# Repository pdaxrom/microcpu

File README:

(c) 2020 sashz <sashz@pdaXrom.org>

For correct work with ftdi jtag, remove ftdi_sio module:

sudo rmmod  ftdi_sio

MICROCPU - 16-bit CPU

Registers:

The processor has eight 16-bit registers. The register 0 (PC) using as program counter.

0 - R0 - PC
1 - R1 - SP
2 - R2 - LR
3 - R3 - V0
4 - R4 - V1
5 - R5 - V2
6 - R6 - V3
7 - R7 - V4

Each register has high byte and low byte:

15 14 13 12 11 10 09 08 | 07 06 05 04 03 02 01 00
        HIGH BYTE       |        LOW BYTE

The processor has 7 addressing modes that can be used by the programmer:

1. Register
2. Immediate
3. Immediate indexed
4. Register indexed
5. Relative

The processor uses five condition code bits or flags:

I - interrupt mask
C - carry flag
Z - zero flag
V - 2s complement overflow
N - negative

Instructions

Machine instructions generally fall into three categories: data movement, arithmetic/logic, and control-flow.
We use the following notation:

<dst> Any destination register
<src> Any source register
<imm> 8-bit immediate
<imm16> 16-bit immediate
<idx> Any register or 4-bit unsigned immediate
<arg1> Any register
<arg2> Any register or 4-bit unsigned immediate
<rel> 11-bit signed immediate

Data Movement Instructions

LDRL <dst>, <src>, <idx> - Load low byte from source address + index
STRL <dst>, <src>, <idx> - Store low byte to source address + index
LDR  <dst>, <src>, <idx> - Load register (2 bytes) from source address + index
STR  <dst>, <src>, <idx> - Store register (2 bytes) to source address + index
SETL <dst>, <imm>        - Copy low byte from constant
SETH <dst>, <imm>        - Copy high byte from constant
MOVL <dst>, <src>        - Copy source low byte to destination low byte
MOVH <dst>, <src>        - Copy source low byte to destination high byte
MOV  <dst>, <src>        - Copy data from source to destination register

Little endian byte order using for LDR and STR.

Examples:
	SETL V0, 0
	SETH V0, $10
	LDRL V1, V0, 0
	SETL V2, 1
	SELH V2, 0
	STR  V1, V0, V2
	MOV V3, V2

Arithmetic and Logic Instructions

ADD  <dst>, <arg1>, <arg2> <dst> = <arg1> + <arg2>           Add
ADDC <dst>, <arg1>, <arg2> <dst> = <arg1> + <arg2>  + flag_C Add with carry
SUB  <dst>, <arg1>, <arg2> <dst> = <arg1> - <arg2>           Subtract
SUBC <dst>, <arg1>, <arg2> <dst> = <arg1> - <arg2>  - flag_C Subtract with carry
SHL  <dst>, <arg1>, <arg2> <dst> = <arg1> << <arg2>          Logic shift left
SHR  <dst>, <arg1>, <arg2> <dst> = <arg1> >> <arg2>          Logic shift right
AND  <dst>, <arg1>, <arg2> <dst> = <arg1> & <arg2>           And
OR   <dst>, <arg1>, <arg2> <dst> = <arg1> | <arg2>           Or
INV  <dst>, <arg1>         <dst> = ~<arg1>                   Inversion
XOR  <dst>, <arg1>, <arg2> <dst> = <arg1> ^ <arg2>           Exclusive Or
SXT  <dst>, <arg1>         <dst> = sign <arg1>               Sign extend

Examples:

	ADD V0, V1, V2
	ADDC V1, V2, 5
	SUB V0, V2, V1
	SHR V0, V0, 1
	SXT V1, V1

Control Flow Instructions

CMP <arg1>, <arg2> Compare
TST <arg1>, <arg2> Test bits

B   <rel> - Branch
BLE <rel> - Branch On Less Than Or Equal Zero
BGE <rel> - Branch On Greater Than Or Equal Zero
BEQ <rel> - Branch On Equal Zero
BCS <rel> - Branch If Carry Set

Examples:

	CMP V0, 0
	BEQ exit
	CMP V0, V1
	BLE loop
	TST V0, 4
	BEQ wait

Assembler directives

<symbol> EQU <exp>      Set a symbol equal to an expression
DB <imm>[,<imm>...]     Define constant byte(s)
DW <imm16>[,<imm16>...] Define constant word(s)
DS <imm16>[,<imm>]      Reserves num bytes of space and initializes them to val (optional, defaul 0).
ALIGN <imm>             Align address to num bytes

Examples:
CONST_ONE EQU 1
CONST_TWO EQU 2
	DB 1, $2, $3, 4, 5
	DB "Hello, World", 0
	DB 'About'
	DW $1234, 8192, 0
	DS 32
	DS 64,$FF
	ALIGN 4

Accembler macro definition

MACRO <name> Start macro
ENDM         End macro

macro parameters start with # and are numbered from 1.

Example:

	MACRO SET
	SETH	#1, /#2
	SETL	#1, #2
	ENDM

	SET V0, $1234

Assembler procedures

<label> PROC                Start procedure
GLOBAL <label>[,<label>...] Add local procedure label as global
ENDP                        End procedure

Example:

get_one PROC
	SET V0, 1
	ADD PC, LR, 3
	ENDP
	
get_1	PROC
	GLOBAL get_2
	SET V0, 1
return	ADD PC, LR, 3
get_2	SET V0, 2
	B return
	ENDP

Microassembler optios:

microasm [-verilog|-binary] <input.asm> [output]

-verilog - create verilog ram file

-binary  - create binary file

By default, the output file is hex file.

Bootloader options:

bootloader <uart port> load <file.bin> [<start address> [<end address>]]

bootloader <uart port> load <file.bin> <start address> <end address>

bootloader <uart port> go [<address>]

load - load a binary file to RAM

save - save RAM to a binary file

go - execute code

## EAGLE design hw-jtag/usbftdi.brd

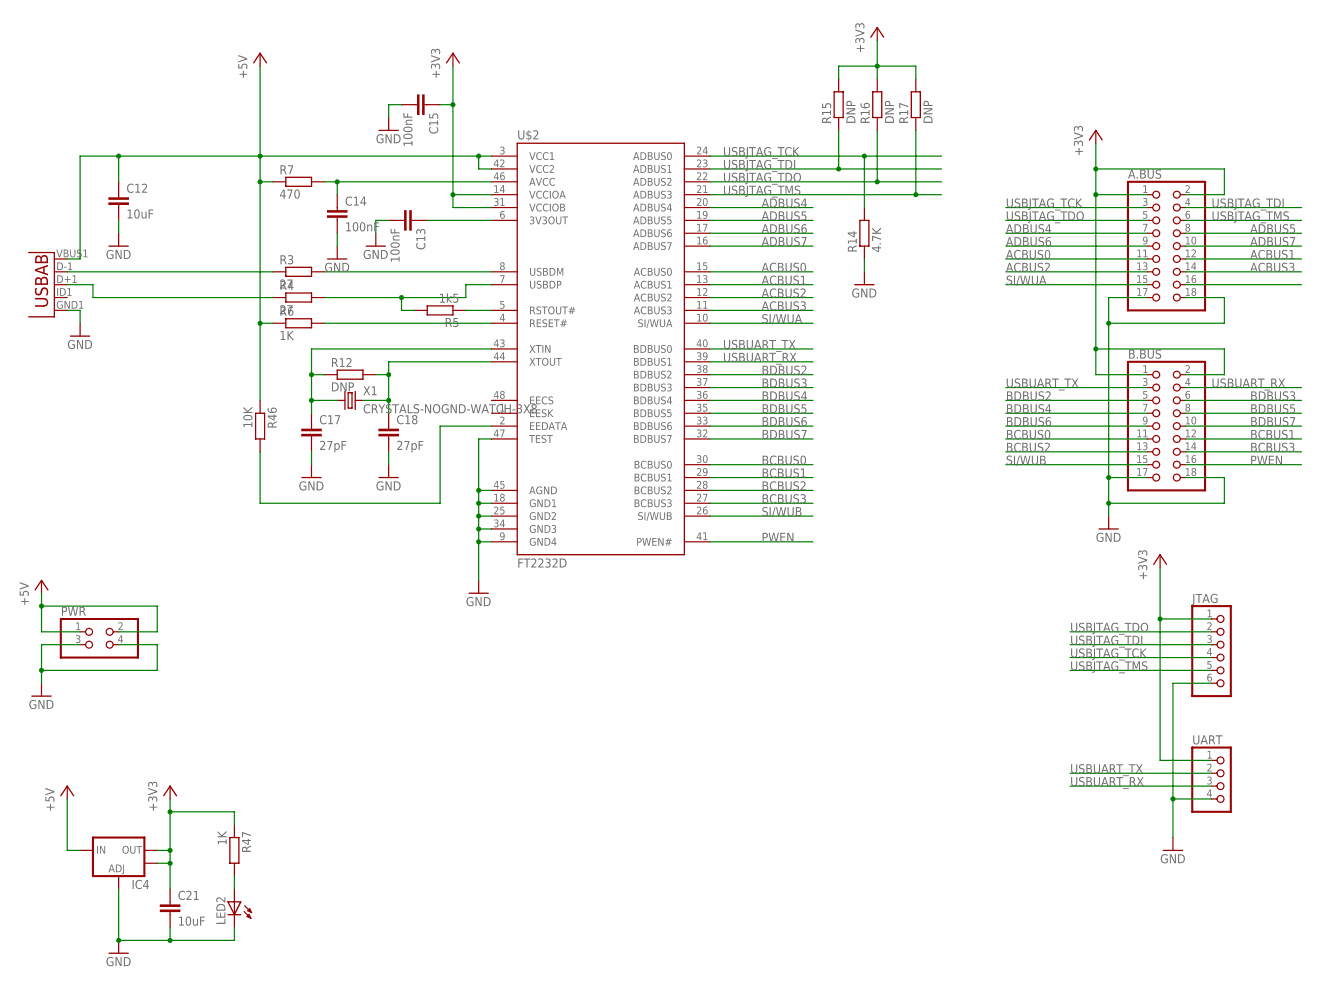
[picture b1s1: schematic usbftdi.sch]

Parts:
A.BUS: PINHD-2X9; 2X09
B.BUS: PINHD-2X9; 2X09
C12, C21: 10uF; C0805
C13, C14, C15: 100nF; C0603
C17, C18: 27pF; C0603
IC4: V_REG_LM1117SOT223; SOT223
JTAG: PINHD-1X6; 1X06
LED2: LEDCHIPLED_0603; CHIPLED_0603
MICROUSB: USB""; USB-MICRO-SMD
PWR: PINHD-2X2; 2X02
R3, R4: 27; R0603
R5: 1k5; R0603
R6, R47: 1K; R0603
R7: 470; R0603
R12, R15, R16, R17: DNP; R0603
R14: 4.7K; R0603
R46: 10K; R0603
U$2: FT2232D; LQFP-48
UART: PINHD-1X4; 1X04
X1: CRYSTALS-NOGND-WATCH-3X8; WATCH-3X8

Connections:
+3V3: A.BUS.1, A.BUS.2, B.BUS.1, B.BUS.2, C15.1, C21.1, IC4.2 (OUT), IC4.4 (OUT), JTAG.1, R15.2, R16.2, R17.2, R47.1, U$2.14 (VCCIOA), U$2.31 (VCCIOB), UART.1
+5V: C12.1, IC4.3 (IN), MICROUSB.VBUS1 (VBUS), PWR.1, PWR.2, R6.1, R7.1, R46.1, U$2.3 (VCC1), U$2.42 (VCC2)
ACBUS0: A.BUS.11, U$2.15 (ACBUS0)
ACBUS1: A.BUS.12, U$2.13 (ACBUS1)
ACBUS2: A.BUS.13, U$2.12 (ACBUS2)
ACBUS3: A.BUS.14, U$2.11 (ACBUS3)
ADBUS4: A.BUS.7, U$2.20 (ADBUS4)
ADBUS5: A.BUS.8, U$2.19 (ADBUS5)
ADBUS6: A.BUS.9, U$2.17 (ADBUS6)
ADBUS7: A.BUS.10, U$2.16 (ADBUS7)
BCBUS0: B.BUS.11, U$2.30 (BCBUS0)
BCBUS1: B.BUS.12, U$2.29 (BCBUS1)
BCBUS2: B.BUS.13, U$2.28 (BCBUS2)
BCBUS3: B.BUS.14, U$2.27 (BCBUS3)
BDBUS2: B.BUS.5, U$2.38 (BDBUS2)
BDBUS3: B.BUS.6, U$2.37 (BDBUS3)
BDBUS4: B.BUS.7, U$2.36 (BDBUS4)
BDBUS5: B.BUS.8, U$2.35 (BDBUS5)
BDBUS6: B.BUS.9, U$2.33 (BDBUS6)
BDBUS7: B.BUS.10, U$2.32 (BDBUS7)
GND: A.BUS.17, A.BUS.18, B.BUS.17, B.BUS.18, C12.2, C13.2, C14.2, C15.2, C17.2, C18.2, C21.2, IC4.1 (ADJ), JTAG.6, LED2.C, MICROUSB.GND1 (GND), PWR.3, PWR.4, R14.1, U$2.9 (GND4), U$2.18 (GND1), U$2.25 (GND2), U$2.34 (GND3), U$2.45 (AGND), U$2.47 (TEST), UART.4
unnamed: MICROUSB.D-1 (D-), R3.1
unnamed: MICROUSB.D+1 (D+), R4.1
unnamed: R3.2, U$2.8 (USBDM)
unnamed: C13.1, U$2.6 (3V3OUT)
unnamed: C14.1, R7.2, U$2.46 (AVCC)
unnamed: R4.2, R5.2, U$2.7 (USBDP)
unnamed: R5.1, U$2.5 (RSTOUT#)
unnamed: R6.2, U$2.4 (RESET#)
unnamed: C17.1, R12.1, U$2.43 (XTIN), X1.1
unnamed: C18.1, R12.2, U$2.44 (XTOUT), X1.2
unnamed: R46.2, U$2.2 (EEDATA)
unnamed: LED2.A, R47.2
PWEN: B.BUS.16, U$2.41 (PWEN#)
SI/WUA: A.BUS.15, U$2.10 (SI/WUA)
SI/WUB: B.BUS.15, U$2.26 (SI/WUB)
USBJTAG_TCK: A.BUS.3, JTAG.4, R14.2, U$2.24 (ADBUS0)
USBJTAG_TDI: A.BUS.4, JTAG.3, R15.1, U$2.23 (ADBUS1)
USBJTAG_TDO: A.BUS.5, JTAG.2, R16.1, U$2.22 (ADBUS2)
USBJTAG_TMS: A.BUS.6, JTAG.5, R17.1, U$2.21 (ADBUS3)
USBUART_RX: B.BUS.4, U$2.39 (BDBUS1), UART.3
USBUART_TX: B.BUS.3, U$2.40 (BDBUS0), UART.2

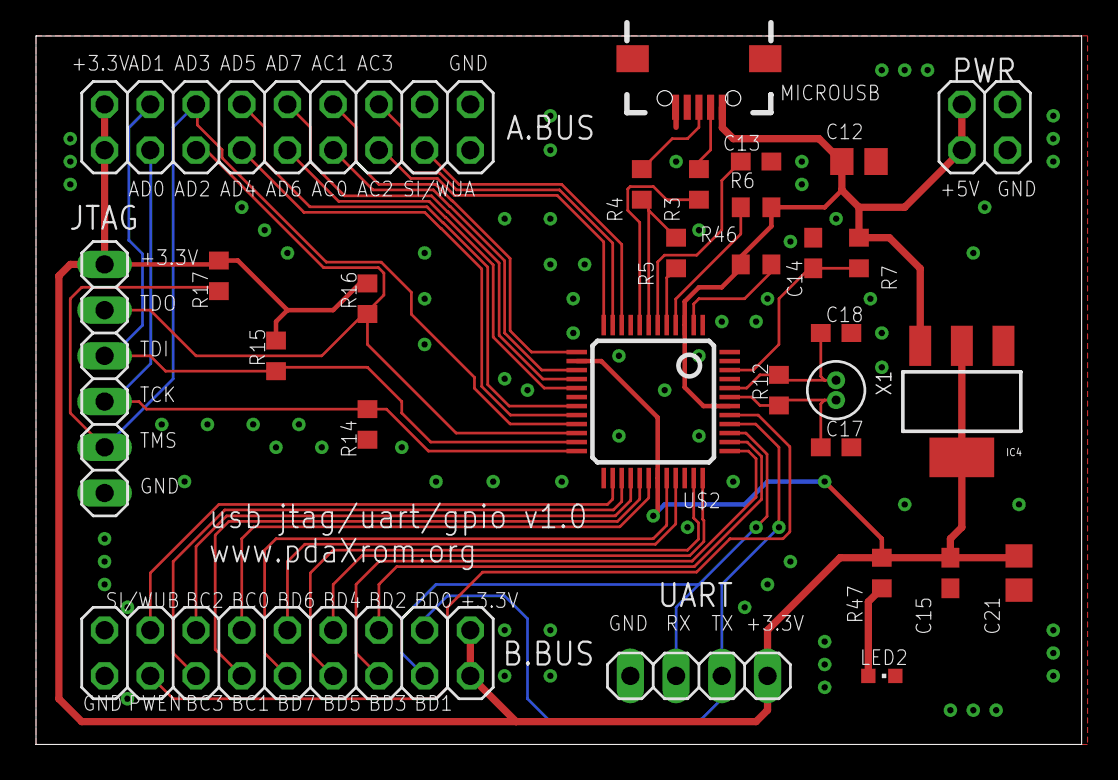
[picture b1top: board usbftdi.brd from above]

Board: 2 copper layers, 58.1 x 39.4 mm, 29 parts (0 on the bottom side), 42 nets.

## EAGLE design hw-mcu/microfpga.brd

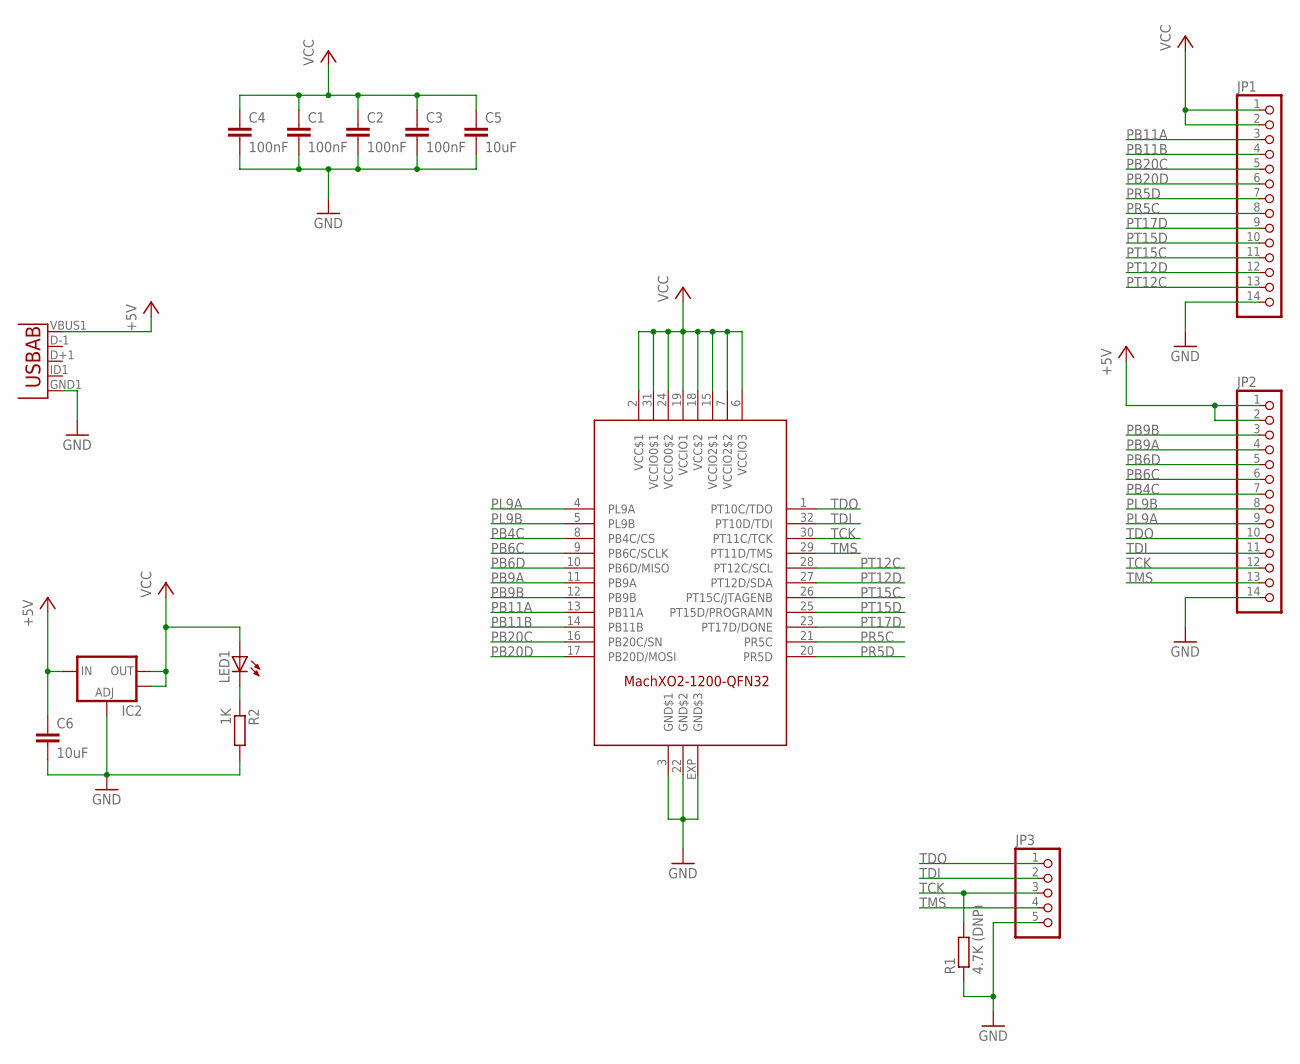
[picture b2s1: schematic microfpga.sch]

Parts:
C1, C2, C3, C4: 100nF; C0603
C5, C6: 10uF; C0805
IC2: V_REG_LM1117SOT223; SOT223
JP1, JP2: PINHD-1X14; 1X14
JP3: PINHD-1X5; 1X05
LED1: LEDCHIPLED_0603; CHIPLED_0603
R1: 4.7K (DNP); R0603
R2: 1K; R0603
U2: USB""; USB-MICRO-SMD
U$1: MACHXO2-1200; QFN32

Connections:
+5V: C6.1, IC2.3 (IN), JP2.1, JP2.2, U2.VBUS1 (VBUS)
GND: C1.2, C2.2, C3.2, C4.2, C5.2, C6.2, IC2.1 (ADJ), JP1.14, JP2.14, JP3.5, R1.1, R2.2, U2.GND1 (GND), U$1.3 (GND$1), U$1.22 (GND$2), U$1.EXP (GND$3)
unnamed: LED1.C, R2.1
PB4C: JP2.7, U$1.8 (PB4C/CS)
PB6C: JP2.6, U$1.9 (PB6C/SCLK)
PB6D: JP2.5, U$1.10 (PB6D/MISO)
PB9A: JP2.4, U$1.11 (PB9A)
PB9B: JP2.3, U$1.12 (PB9B)
PB11A: JP1.3, U$1.13 (PB11A)
PB11B: JP1.4, U$1.14 (PB11B)
PB20C: JP1.5, U$1.16 (PB20C/SN)
PB20D: JP1.6, U$1.17 (PB20D/MOSI)
PL9A: JP2.9, U$1.4 (PL9A)
PL9B: JP2.8, U$1.5 (PL9B)
PR5C: JP1.8, U$1.21 (PR5C)
PR5D: JP1.7, U$1.20 (PR5D)
PT12C: JP1.13, U$1.28 (PT12C/SCL)
PT12D: JP1.12, U$1.27 (PT12D/SDA)
PT15C: JP1.11, U$1.26 (PT15C/JTAGENB)
PT15D: JP1.10, U$1.25 (PT15D/PROGRAMN)
PT17D: JP1.9, U$1.23 (PT17D/DONE)
TCK: JP2.12, JP3.3, R1.2, U$1.30 (PT11C/TCK)
TDI: JP2.11, JP3.2, U$1.32 (PT10D/TDI)
TDO: JP2.10, JP3.1, U$1.1 (PT10C/TDO)
TMS: JP2.13, JP3.4, U$1.29 (PT11D/TMS)
VCC: C1.1, C2.1, C3.1, C4.1, C5.1, IC2.2 (OUT), IC2.4 (OUT), JP1.1, JP1.2, LED1.A, U$1.2 (VCC$1), U$1.6 (VCCIO3), U$1.7 (VCCIO2$2), U$1.15 (VCCIO2$1), U$1.18 (VCC$2), U$1.19 (VCCIO1), U$1.24 (VCCIO0$2), U$1.31 (VCCIO0$1)

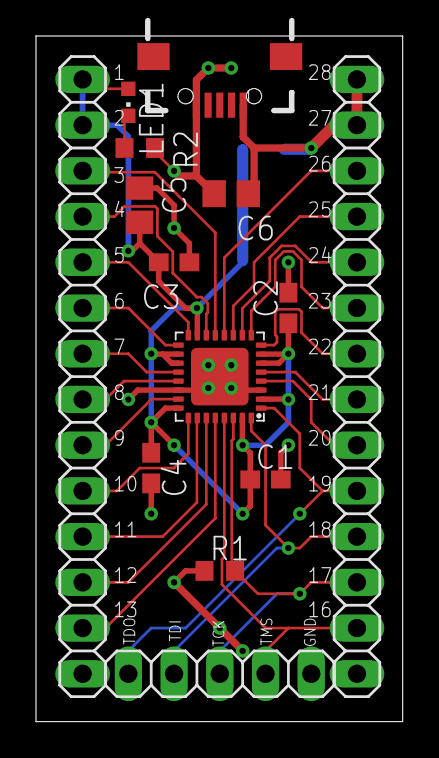
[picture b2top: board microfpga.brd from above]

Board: 2 copper layers, 20.4 x 38.1 mm, 15 parts (1 on the bottom side), 26 nets.

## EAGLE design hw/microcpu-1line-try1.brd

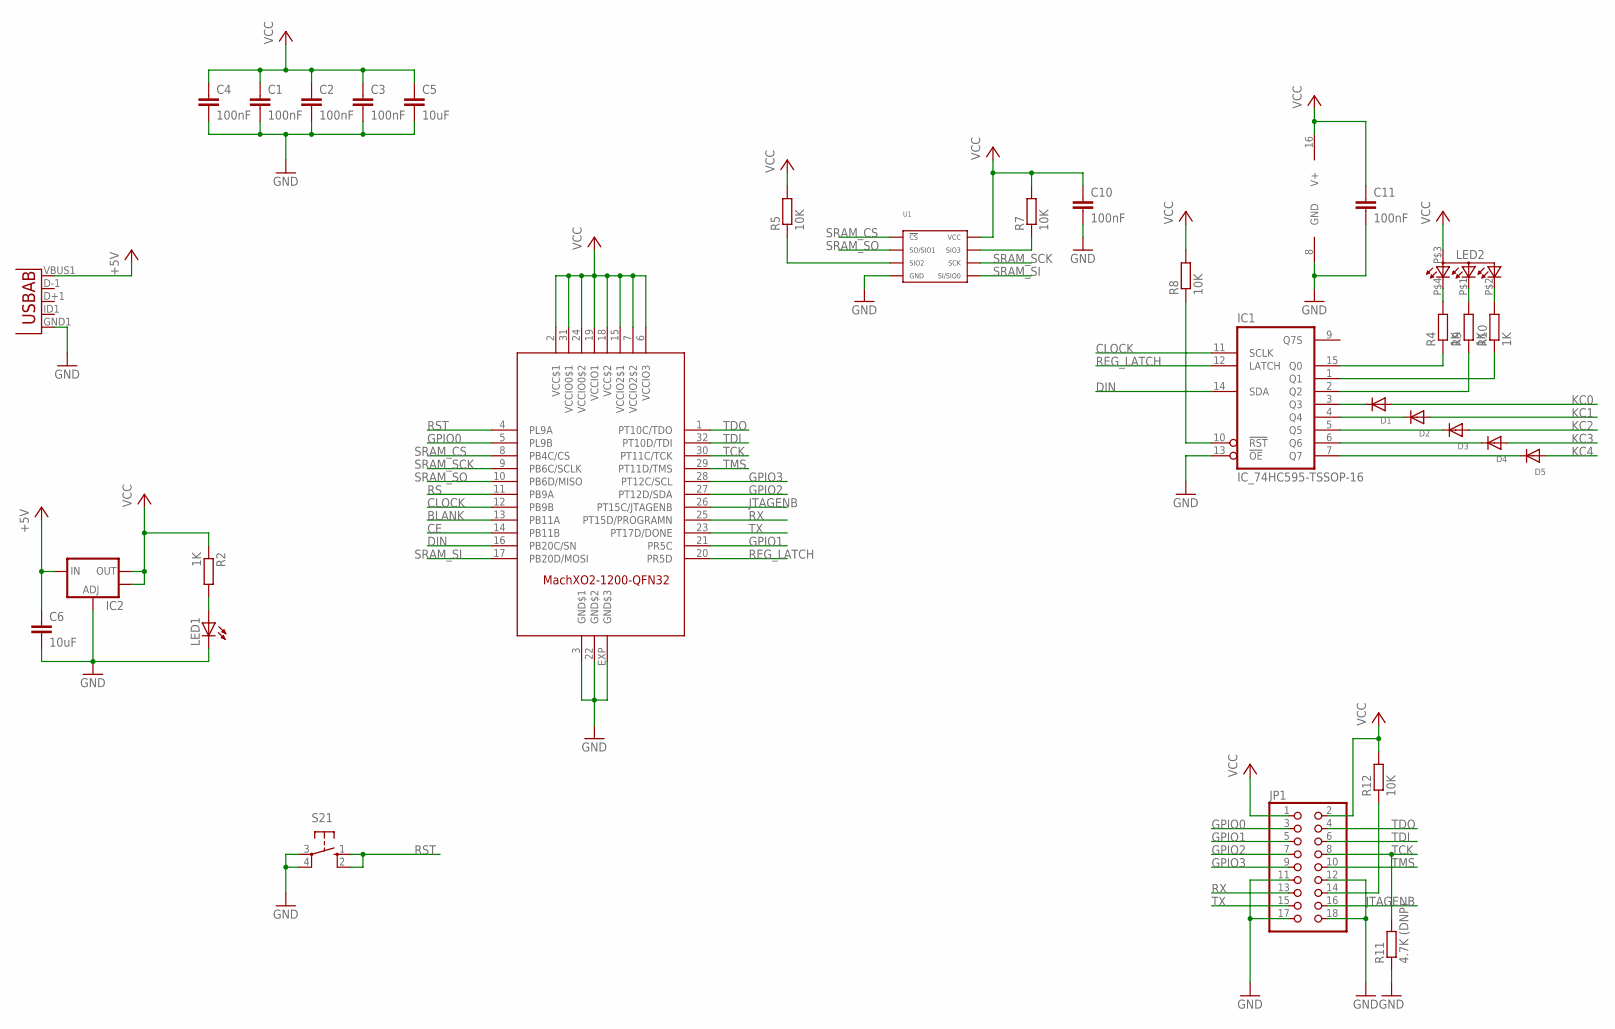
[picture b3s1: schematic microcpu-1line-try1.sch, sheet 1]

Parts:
C1, C2, C3, C4, C10, C11: 100nF; C0603
C5, C6: 10uF; C0805
D1, D2, D3, D4, D5: DIODESOD-123; SOD-123
IC1: IC_74HC595-TSSOP-16; TSSOP-16
IC2: V_REG_LM1117SOT223; SOT223
JP1: PINHD-2X9/90; 2X09/90
LED1: LEDCHIPLED_0603; CHIPLED_0603
LED2: 19-237/R6GHBHC-A04/2T
R2, R4, R9, R10: 1K; R0603
R5, R7, R8, R12: 10K; R0603
R11: 4.7K (DNP); R0603
S21: 10-XX; B3F-10XX
U1: 23A1024/23LC1024-I/SN; 23A1024_SOIC-8
U2: USB""; USB-MICRO-SMD
U$1: MACHXO2-1200; QFN32

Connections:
+5V: C6.1, IC2.3 (IN), U2.VBUS1 (VBUS)
BLANK: U$1.13 (PB11A); also elsewhere on the board
CE: U$1.14 (PB11B); also elsewhere on the board
CLOCK: IC1.11 (SCLK), U$1.12 (PB9B); also elsewhere on the board
DIN: IC1.14 (SDA), U$1.16 (PB20C/SN); also elsewhere on the board
GND: C1.2, C2.2, C3.2, C4.2, C5.2, C6.2, C10.2, C11.2, IC1.8 (GND), IC1.13 (!OE), IC2.1 (ADJ), JP1.11, JP1.12, JP1.17, JP1.18, LED1.C, R11.1, S21.3, S21.4 (P1), U1.4 (GND), U2.GND1 (GND), U$1.3 (GND$1), U$1.22 (GND$2), U$1.EXP (GND$3); also elsewhere on the board
GPIO0: JP1.3, U$1.5 (PL9B)
GPIO1: JP1.5, U$1.21 (PR5C)
GPIO2: JP1.7, U$1.27 (PT12D/SDA)
GPIO3: JP1.9, U$1.28 (PT12C/SCL)
JTAGENB: JP1.16, U$1.26 (PT15C/JTAGENB)
KC0: D1.A; also elsewhere on the board
KC1: D2.A; also elsewhere on the board
KC2: D3.A; also elsewhere on the board
KC3: D4.A; also elsewhere on the board
KC4: D5.A; also elsewhere on the board
unnamed: LED1.A, R2.2
unnamed: R7.1, U1.7 (SIO3)
unnamed: IC1.10 (!RST), R8.1
unnamed: R5.1, U1.3 (SIO2)
unnamed: LED2.P$4 (CRED), R4.2
unnamed: LED2.P$1 (CBLUE), R9.2
unnamed: LED2.P$2 (CGREEN), R10.2
unnamed: IC1.15 (Q0), R4.1
unnamed: IC1.1 (Q1), R10.1
unnamed: IC1.2 (Q2), R9.1
unnamed: JP1.14, R12.1
unnamed: D1.C, IC1.3 (Q3)
unnamed: D2.C, IC1.4 (Q4)
unnamed: D3.C, IC1.5 (Q5)
unnamed: D4.C, IC1.6 (Q6)
unnamed: D5.C, IC1.7 (Q7)
REG_LATCH: IC1.12 (LATCH), U$1.20 (PR5D)
RS: U$1.11 (PB9A); also elsewhere on the board
RST: S21.1 (S), S21.2 (S1), U$1.4 (PL9A)
RX: JP1.13, U$1.25 (PT15D/PROGRAMN)
SRAM_CS: U1.1 (CS'), U$1.8 (PB4C/CS)
SRAM_SCK: U1.6 (SCK), U$1.9 (PB6C/SCLK)
SRAM_SI: U1.5 (SI/SIO0), U$1.17 (PB20D/MOSI)
SRAM_SO: U1.2 (SO/SIO1), U$1.10 (PB6D/MISO)
TCK: JP1.8, R11.2, U$1.30 (PT11C/TCK); also elsewhere on the board
TDI: JP1.6, U$1.32 (PT10D/TDI); also elsewhere on the board
TDO: JP1.4, U$1.1 (PT10C/TDO); also elsewhere on the board
TMS: JP1.10, U$1.29 (PT11D/TMS); also elsewhere on the board
TX: JP1.15, U$1.23 (PT17D/DONE)
VCC: C1.1, C2.1, C3.1, C4.1, C5.1, C10.1, C11.1, IC1.16 (V+), IC2.2 (OUT), IC2.4 (OUT), JP1.1, JP1.2, LED2.P$3 (A), R2.1, R5.2, R7.2, R8.2, R12.2, U1.8 (VCC), U$1.2 (VCC$1), U$1.6 (VCCIO3), U$1.7 (VCCIO2$2), U$1.15 (VCCIO2$1), U$1.18 (VCC$2), U$1.19 (VCCIO1), U$1.24 (VCCIO0$2), U$1.31 (VCCIO0$1); also elsewhere on the board

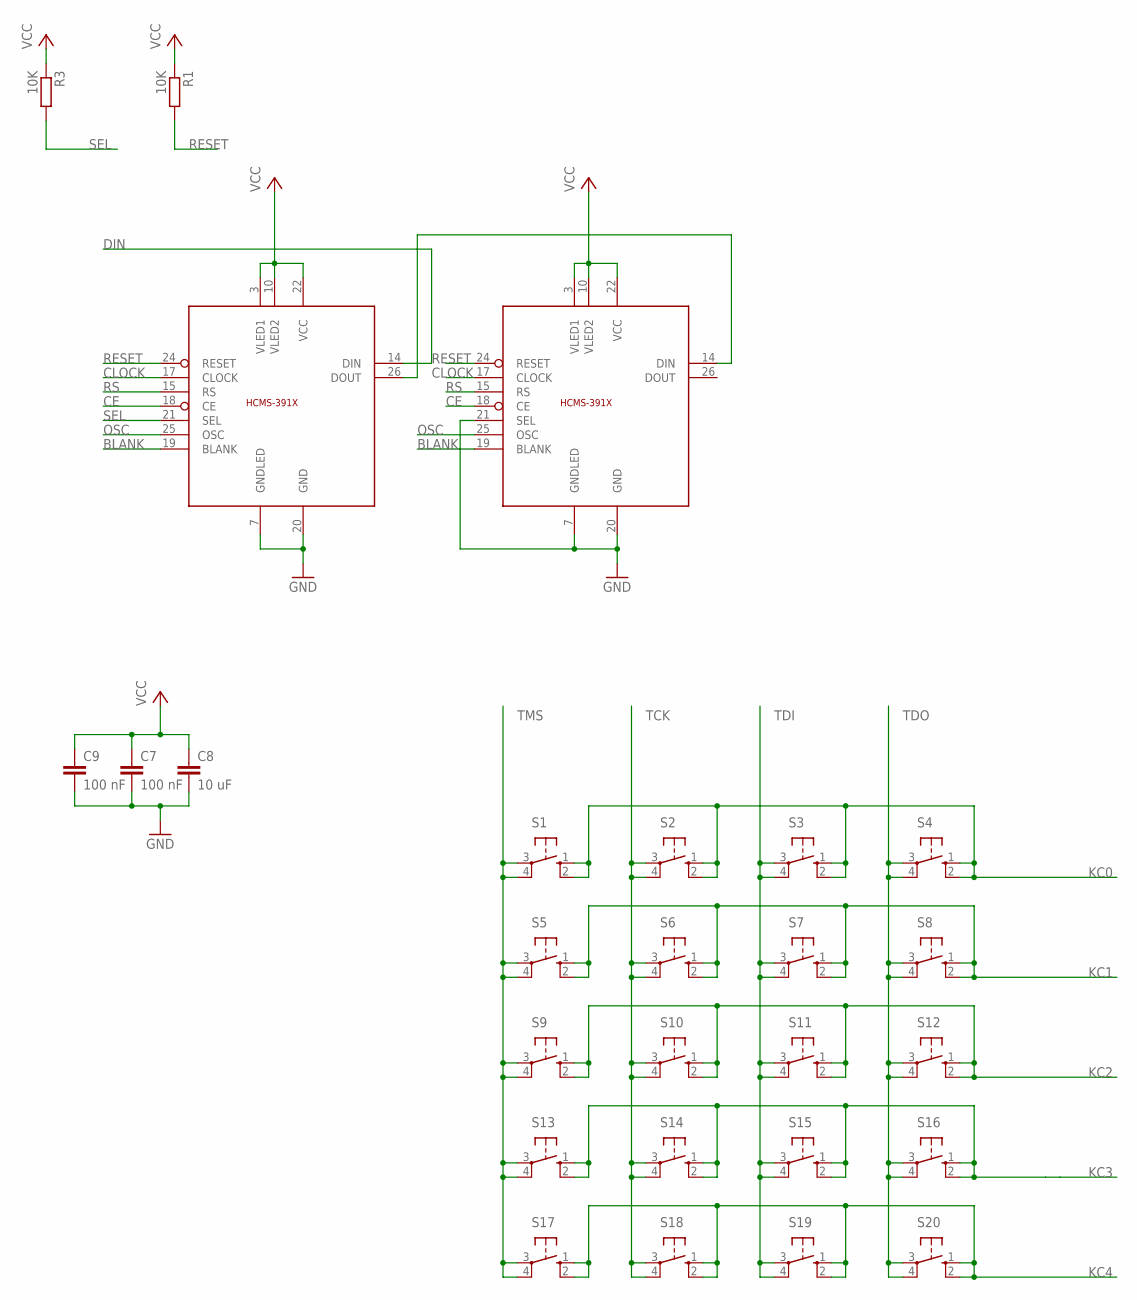
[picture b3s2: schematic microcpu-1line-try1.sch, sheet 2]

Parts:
C7, C9: 100 nF; C0603K
C8: 10 uF; C0805K
R1, R3: 10K; R0603
S1, S2, S3, S4, S5, S6, S7, S8, S9, S10, S11, S12, S13, S14, S15, S16, S17, S18, S19, S20: 10-XX; B3F-10XX
U$2, U$3: HCMS-391X

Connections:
BLANK: U$2.19 (BLANK), U$3.19 (BLANK); also elsewhere on the board
CE: U$2.18 (CE), U$3.18 (CE); also elsewhere on the board
CLOCK: U$2.17 (CLOCK), U$3.17 (CLOCK); also elsewhere on the board
DIN: U$2.14 (DIN); also elsewhere on the board
GND: C7.2, C8.2, C9.2, U$2.7 (GNDLED), U$2.20 (GND), U$3.7 (GNDLED), U$3.20 (GND), U$3.21 (SEL); also elsewhere on the board
KC0: S1.1 (S), S1.2 (S1), S2.1 (S), S2.2 (S1), S3.1 (S), S3.2 (S1), S4.1 (S), S4.2 (S1); also elsewhere on the board
KC1: S5.1 (S), S5.2 (S1), S6.1 (S), S6.2 (S1), S7.1 (S), S7.2 (S1), S8.1 (S), S8.2 (S1); also elsewhere on the board
KC2: S9.1 (S), S9.2 (S1), S10.1 (S), S10.2 (S1), S11.1 (S), S11.2 (S1), S12.1 (S), S12.2 (S1); also elsewhere on the board
KC3: S13.1 (S), S13.2 (S1), S14.1 (S), S14.2 (S1), S15.1 (S), S15.2 (S1), S16.1 (S), S16.2 (S1); also elsewhere on the board
KC4: S17.1 (S), S17.2 (S1), S18.1 (S), S18.2 (S1), S19.1 (S), S19.2 (S1), S20.1 (S), S20.2 (S1); also elsewhere on the board
unnamed: U$2.26 (DOUT), U$3.14 (DIN)
OSC: U$2.25 (OSC), U$3.25 (OSC)
RESET: R1.2, U$2.24 (RESET), U$3.24 (RESET)
RS: U$2.15 (RS), U$3.15 (RS); also elsewhere on the board
SEL: R3.2, U$2.21 (SEL)
TCK: S2.3, S2.4 (P1), S6.3, S6.4 (P1), S10.3, S10.4 (P1), S14.3, S14.4 (P1), S18.3, S18.4 (P1); also elsewhere on the board
TDI: S3.3, S3.4 (P1), S7.3, S7.4 (P1), S11.3, S11.4 (P1), S15.3, S15.4 (P1), S19.3, S19.4 (P1); also elsewhere on the board
TDO: S4.3, S4.4 (P1), S8.3, S8.4 (P1), S12.3, S12.4 (P1), S16.3, S16.4 (P1), S20.3, S20.4 (P1); also elsewhere on the board
TMS: S1.3, S1.4 (P1), S5.3, S5.4 (P1), S9.3, S9.4 (P1), S13.3, S13.4 (P1), S17.3, S17.4 (P1); also elsewhere on the board
VCC: C7.1, C8.1, C9.1, R1.1, R3.1, U$2.3 (VLED1), U$2.10 (VLED2), U$2.22 (VCC), U$3.3 (VLED1), U$3.10 (VLED2), U$3.22 (VCC); also elsewhere on the board

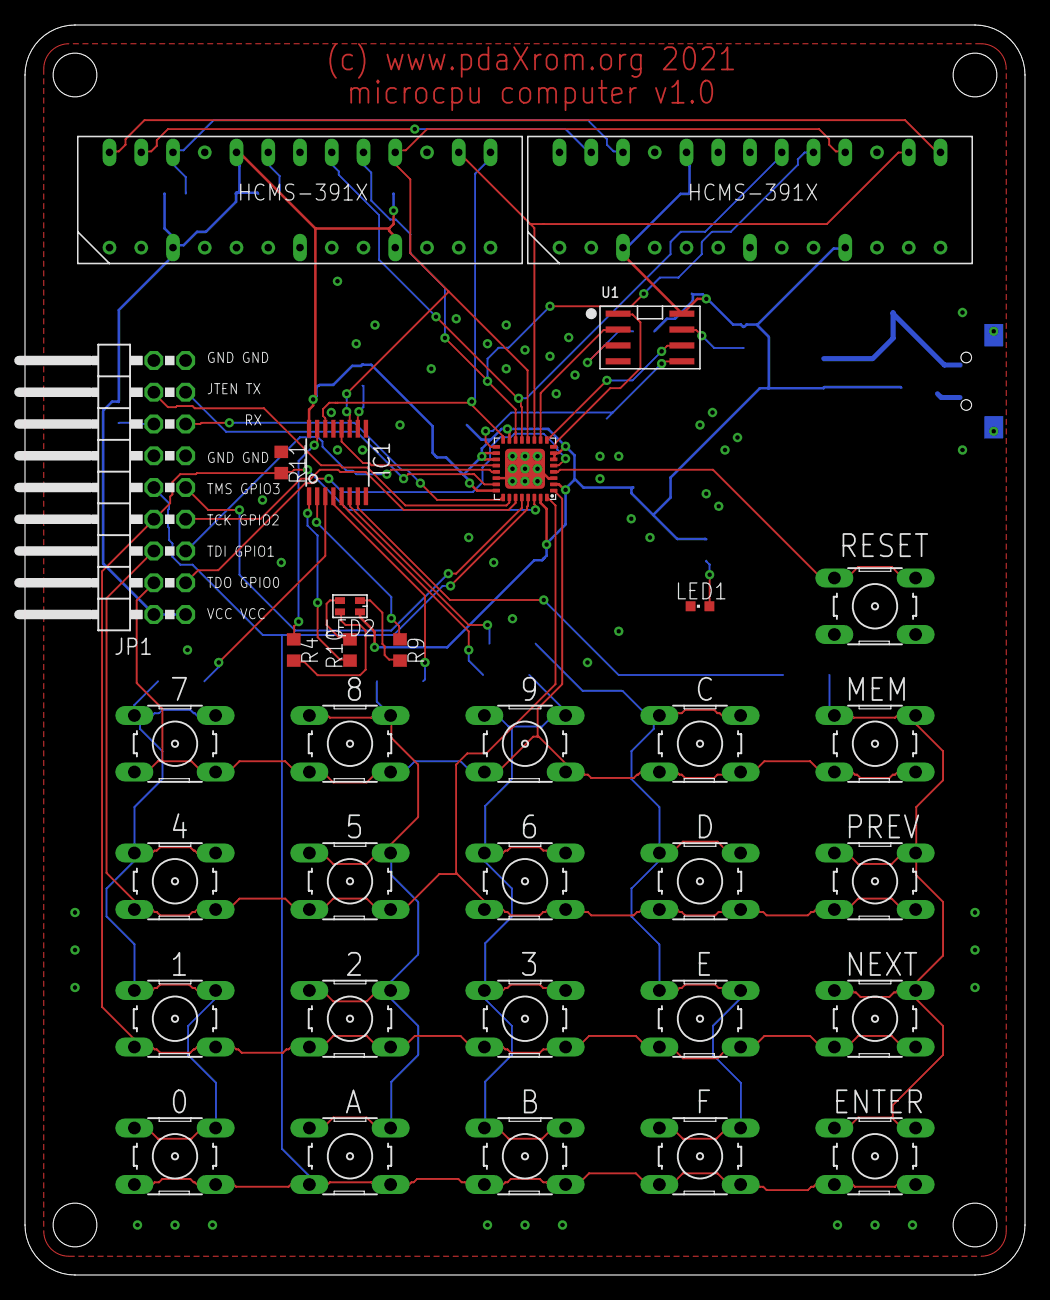
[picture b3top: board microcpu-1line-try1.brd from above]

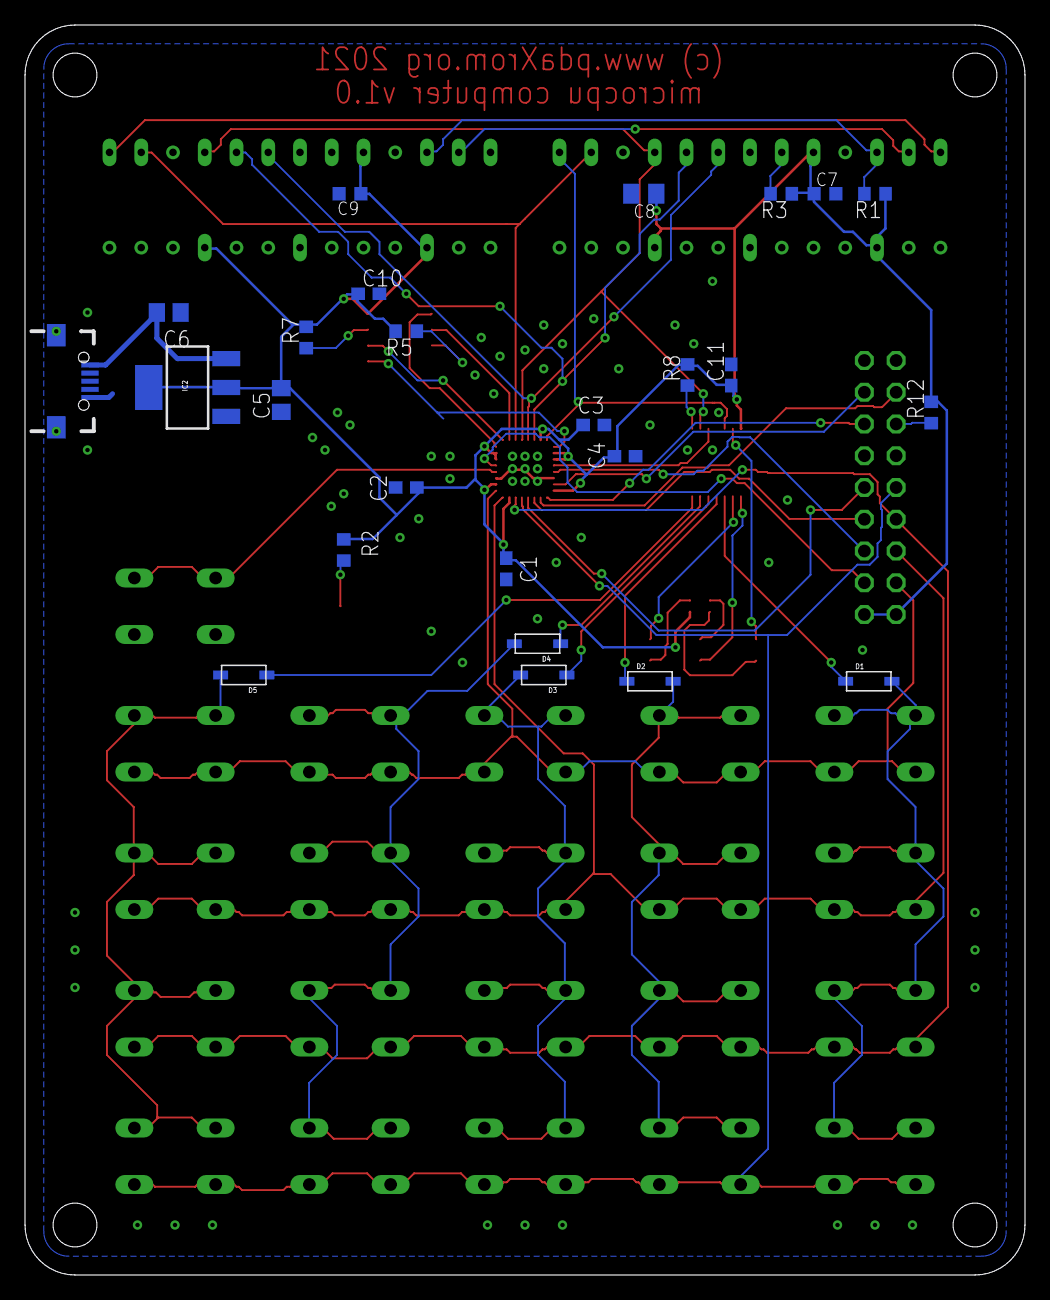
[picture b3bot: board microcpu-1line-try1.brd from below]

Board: 2 copper layers, 80.0 x 100.0 mm, 58 parts (25 on the bottom side), 50 nets.

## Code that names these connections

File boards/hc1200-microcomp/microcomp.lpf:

BLOCK RESETPATHS ;
BLOCK ASYNCPATHS ;
IOBUF ALLPORTS IO_TYPE=LVCMOS33 ;
IOBUF PORT "res" PULLMODE=UP IO_TYPE=LVCMOS33 ;
IOBUF PORT "rx" PULLMODE=NONE IO_TYPE=LVCMOS33 ;
IOBUF PORT "gpio[0]" PULLMODE=NONE IO_TYPE=LVCMOS33 ;
IOBUF PORT "gpio[1]" PULLMODE=NONE IO_TYPE=LVCMOS33 ;
IOBUF PORT "gpio[2]" PULLMODE=NONE IO_TYPE=LVCMOS33 ;
IOBUF PORT "gpio[3]" PULLMODE=NONE IO_TYPE=LVCMOS33 ;
IOBUF PORT "tx" PULLMODE=NONE IO_TYPE=LVCMOS33 ;
LOCATE COMP "res" SITE "PL9A" ;
LOCATE COMP "rx" SITE "PT15D" ;
LOCATE COMP "tx" SITE "PT17D" ;
LOCATE COMP "gpio[0]" SITE "PL9B" ;
LOCATE COMP "gpio[1]" SITE "PR5C" ;
LOCATE COMP "gpio[2]" SITE "PT12D" ;
LOCATE COMP "gpio[3]" SITE "PT12C" ;
SYSCONFIG JTAG_PORT=DISABLE MUX_CONFIGURATION_PORTS=ENABLE ;
LOCATE COMP "gpio_key_row[0]" SITE "PT11D" ;
LOCATE COMP "gpio_key_row[1]" SITE "PT11C" ;
LOCATE COMP "gpio_key_row[2]" SITE "PT10D" ;
LOCATE COMP "gpio_key_row[3]" SITE "PT10C" ;
LOCATE COMP "gpio_miso" SITE "PB6D" ;
LOCATE COMP "gpio_mcs" SITE "PB4C" ;
LOCATE COMP "gpio_mosi" SITE "PB20D" ;
LOCATE COMP "gpio_msck" SITE "PB6C" ;
LOCATE COMP "gpio_reg_latch" SITE "PR5D" ;
LOCATE COMP "gpio_din" SITE "PB20C" ;
LOCATE COMP "gpio_clk" SITE "PB9B" ;
LOCATE COMP "gpio_ce" SITE "PB11B" ;
LOCATE COMP "gpio_blank" SITE "PB11A" ;
LOCATE COMP "gpio_rs" SITE "PB9A" ;
IOBUF PORT "gpio_key_row[0]" PULLMODE=DOWN IO_TYPE=LVCMOS33 ;
IOBUF PORT "gpio_key_row[1]" PULLMODE=DOWN IO_TYPE=LVCMOS33 ;
IOBUF PORT "gpio_key_row[2]" PULLMODE=DOWN IO_TYPE=LVCMOS33 ;
IOBUF PORT "gpio_key_row[3]" PULLMODE=DOWN IO_TYPE=LVCMOS33 ;
IOBUF PORT "gpio_miso" PULLMODE=NONE IO_TYPE=LVCMOS33 ;
IOBUF PORT "gpio_rs" PULLMODE=NONE IO_TYPE=LVCMOS33 ;
IOBUF PORT "gpio_blank" PULLMODE=NONE IO_TYPE=LVCMOS33 ;
IOBUF PORT "gpio_ce" PULLMODE=NONE IO_TYPE=LVCMOS33 ;
IOBUF PORT "gpio_clk" PULLMODE=NONE IO_TYPE=LVCMOS33 ;
IOBUF PORT "gpio_din" PULLMODE=NONE IO_TYPE=LVCMOS33 ;
IOBUF PORT "gpio_mcs" PULLMODE=NONE IO_TYPE=LVCMOS33 ;
IOBUF PORT "gpio_mosi" PULLMODE=NONE IO_TYPE=LVCMOS33 ;
IOBUF PORT "gpio_msck" PULLMODE=NONE IO_TYPE=LVCMOS33 ;
IOBUF PORT "gpio_reg_latch" PULLMODE=NONE IO_TYPE=LVCMOS33 ;

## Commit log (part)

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2020-11-28 initial
2020-11-28 update project
2020-11-28 moved to rtl subdir
2020-11-28 assembler initial
2020-11-28 second pass
2020-11-29 hex output
2020-11-29 remove comments
2020-11-29 skip empty strings
2020-11-29 pseudo op db
2020-11-29 pseudo op dw
2020-11-29 pseudo ds and align ops
2020-11-29 readme
2020-11-30 demo initial
2020-11-30 verilog output
2020-11-30 testbench
2020-12-01 working cpu (no cmp/jmp ops)
2020-12-01 working led output
2020-12-01 compare/branches ops
2020-12-02 two passes assembler
2020-12-02 fix wrong address calculation on first pass
2020-12-02 source format
2020-12-02 extended ops, branch related op
2020-12-02 updated examples
2020-12-02 16 bit initial
2020-12-04 movl movh commands
2020-12-04 ALU, optimization
2020-12-05 initial fixes
2020-12-05 macro initial
2020-12-05 enable bytes loading
2020-12-05 fixes
2020-12-07 fix assembler, cpu optimization
2020-12-07 examples register counter and counter from memory
2020-12-07 reset fixed
2020-12-07 macroassember expand macros and args
2020-12-07 better error handling
2020-12-08 subroutine, push, pop, set, nop
2020-12-08 missed beq instruction
2020-12-08 sext, addc, subc
2020-12-08 alu moved to separate block. sets/gets/tst commands
2020-12-08 microcomp with uart
2020-12-09 detach jtag channel from ftdi
2020-12-09 uart demos
2020-12-09 gpio support
2020-12-09 added gpio to project
2020-12-09 equ pseudo op
2020-12-10 removed unnecessary code
2020-12-10 proc, global
2020-12-10 better errors handling
2020-12-11 fixed wrong shift for arg2 register
2020-12-11 little optimization
2020-12-11 fixed related offset, inv, xor
2020-12-12 fixed related offset size
2020-12-12 max7219 initial
2020-12-12 delay for display initialization
2020-12-12 disable debug dump
2020-12-13 ldrh, strh replaced with 16-bit ldr, str; related branch now use words offset
2020-12-13 show error for extra symbols in assembled line, gets/sets disabled for better implementation
2020-12-13 Timer initial
2020-12-13 fixed interrupt line
2020-12-13 missed file
2020-12-15 HCMS driver example
2020-12-15 uart bootloader initial
2020-12-15 fixed char value
2020-12-15 org directive
2020-12-15 bootloader little optimization
2020-12-16 autocreate output file
2020-12-16 fixed bootloader size in 256 byte block
2020-12-16 microcomp demos
2020-12-16 moved to microcomp
2020-12-16 Set theme jekyll-theme-hacker
2020-12-16 github pages initial
2020-12-16 page
2020-12-16 Create CNAME
2020-12-16 Update CNAME
2020-12-16 photos
2020-12-16 fix top link
2020-12-16 theme
2020-12-16 Set theme jekyll-theme-modernist
2020-12-17 removed condition flags, added conditional branches
2020-12-18 super/user mode
2020-12-18 timer irq initial
2020-12-19 fixed timer example
2020-12-19 Readme update
2020-12-19 fixed top links
2020-12-19 missed opcodes
2020-12-19 not working yet
2020-12-22 include directive, memmapping for microcomp
2020-12-22 moved IO to
2020-12-23 virtual memory support
2020-12-24 uart monitor initial
2020-12-24 dump
2020-12-25 align fixed
2020-12-25 memmap interrupt fixed
2020-12-25 calculate offset on pass two
2020-12-25 removed nonnecessary gpio direction mask for output register
2020-12-25 get/set interrupted address
2020-12-25 spi ram read write initial
2020-12-26 SQI mode support
2020-12-26 virtual memory initial support
2020-12-26 remove spaces at end of line
2020-12-26 push/pop optimization
2020-12-26 fixed crash with uninited pointer, dw write little endian words
2020-12-26 long jump and jsr (both use lr register)
2020-12-26 19MHz by default
2020-12-27 26.6MHz, upload by 8 bytes packets
2020-12-27 14 bytes packets
2020-12-27 virtual memory control moved to bootloader
2021-02-20 fixed build
2021-02-20 missed system ram include
2021-02-23 removed programmer info from project
2021-02-24 HCMS display module for bootloader
2021-02-24 display text
2021-03-17 microcpu board
2021-03-31 fixed for microcpu hardware, use fram
2021-03-31 keyboard row data
2021-04-01 outreg demo
2021-04-01 flush rampages to fram/sram
2021-04-01 setreg
2021-04-01 rgb led example
2021-04-01 default boot address ix 0x0800, fixed flush serial data
2021-04-01 wp pullup for fram, diodes for matrix keyboard
2021-04-02 read keys sample
2021-04-04 dirty rampage flag, fixed bit comparing op and pseudo op
2021-04-04 fixed macros jsr and jmp
2021-04-04 check summ calculation
2021-04-04 fixed jsr/bsr macros
2021-04-04 modules support
2021-04-05 Update README.md
    microasm instructions updated
2021-04-05 monitor updated
2021-04-05 mcu hardware
2021-04-05 mcu page
2021-04-05 microcpu mcu hardware
2021-04-05 jtag hardware
2021-04-05 fixed links
2021-06-12 build modules
2021-06-12 putchar to display
2021-06-12 putsring
2021-06-13 getstring
2021-06-18 fixed delete last char by prev button
2025-10-26 fix code style
2025-10-26 fix(asm): fix buffer overflows in operand and get_bytes functions
    - Replace variable-length arrays with fixed-size buffers (256 bytes)
    - Add bounds checks in operand() to prevent buffer overflow
    - Fix loop condition in get_bytes() to avoid infinite loops
    - Use safe string copy with strncpy and null termination
    - Add output buffer size checks before writing
    - Correct typo in CONSTANT_VALUE_TOO_BIG error
2025-10-26 fix(asm): add checks for memory allocation failures
    - Check return values of malloc, realloc, and strdup in add_label, add_proc, and add_macro
    - Free allocated memory on strdup failure to prevent leaks
    - Set appropriate error codes on allocation failures
2025-10-26 fix(asm): fix expression parsing issues
    - Add division by zero checks in exp6() for / and % operators
    - Replace variable-length arrays with fixed-size buffers in operand, find_opcode_in_string, and find_register_in_string
    - Add bounds checks to prevent buffer overflows in string parsing functions
    - In operand(), error on unresolved labels in pass 2 instead of silently returning 0
2025-10-26 fix(asm): fix file handling issues
    - Add check for argc >= 2 in main() to prevent invalid argv[1] access
    - Change fseek check to error and exit if rewinding file fails for pass 2
    - Remove invalid 'else' clause in main() that was causing compilation errors
2025-10-26 fix(asm): resolve potential bugs in assembler
    - Correct SKIP_TOKEN macro logic error
    - Fix memory leaks in add_macro function
    - Make label and proc lookups case-insensitive
2025-10-26 fix(bootloader): clean output files
2025-10-26 fix(asm): compilation warnings.
2026-01-29 add documentation
2026-01-29 fix remove old README
2026-05-13 test(testbench): add CPU ISA regression harness
2026-05-13 test(testbench): add MMIO and bootloader smoke tests
2026-05-13 test(testbench): cover bootloader UART commands
2026-05-13 test(testbench): add GPIO MMIO coverage
2026-05-13 test(testbench): add bus write trace checks
2026-05-13 test(testbench): cover const4 edge cases
2026-05-13 test(testbench): cover bootloader load and bus reads
2026-05-13 test(testbench): cover interrupt corner cases
2026-05-13 test: add top-level regression target
2026-05-13 test(testbench): add board-level smoke tests
2026-05-13 test(testbench): cover board UART RX and memmap boundaries
2026-05-21 feat(microemu): add hc1200-mcu emulator
2026-05-21 feat(asm): add 32-bit arithmetic support
2026-05-21 feat(asm): add FIS floating point support
2026-05-21 fix(asm): round FIS16 division
2026-05-21 feat(microemu): add hc1200-cpu board
2026-05-21 feat(microemu): add hc1200-microcomp emulation
2026-05-21 test(microemu): add FRAM virtual memory smoke test
2026-05-21 feat(microemu): add interactive UART benchmarks
2026-05-21 perf(asm): optimize fis32 arithmetic
2026-05-21 feat(smallc): add microcpu backend
    Vendor Hendrix Small-C 2.2 Rev.117 sources, add a host build with microcpu code generation, runtime helpers, ABI documentation, and initial emulator-backed tests.
2026-05-21 feat(smallc): harden microcpu ABI and tests
    Document the generated ABI, strengthen calls, comparisons, chars, pointers, arrays, and runtime helpers, and expand the Small-C test runner through test 036.
2026-05-22 feat(smallc): add microcpu memory model tests
    Cover local addresses, local arrays, pointer arithmetic, char arrays, char pointers, string literals, and strlen for the Small-C microcpu backend.
2026-05-22 test(smallc): run microcpu tests under microemu
    Compile and assemble tests into build/tests, run each binary through microemu with stop-on-self-branch, compare final V0 against expected.txt, and document the test halt convention.
2026-05-22 test(smallc): cover core expressions and loop control
    Add Small-C microcpu tests for unary, bitwise, shift, logical short-circuit, compound assignment, increment/decrement, for, do/while, break, and continue, and document the confirmed ABI behavior.
2026-05-22 test(smallc): cover switch goto labels and initializers
    Add tests for goto, labels, nested control flow, switch/case/default, global initializers, string escapes, and sizeof. Implement the microcpu switch runtime helper and document initialized data layou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
2026-05-22 feat(smallc): add tiny libc memory and string helpers
    Implement memset, memcpy, memcmp, strcpy, strcmp, and strchr in the microcpu runtime, add tests through 136, and document the helper ABI and current prototype limits.
2026-05-22 feat(smallc): add UART stdio runtime helpers
2026-05-22 feat(smallc): add struct typedef and enum support
2026-05-22 test(smallc): add self-hosting smoke checks
2026-05-22 feat(smallc): add minimal include and define preprocessing
2026-05-22 feat(smallc): add simple function-like macro preprocessing
2026-05-22 fix(smallc): harden selfhost symbol and prototype handling
2026-05-22 fix(smallc): add void static and longer identifiers
2026-05-22 feat(asm): add conditional assembly controls
    Add IF/IFDEF/IFNDEF/ELSE/ENDIF handling with pass-1 decisions and a 32-level nesting limit.
    Add -D/--define and -U/--undef CLI support, smoke coverage, and assembler documentation.
2026-05-22 feat(asm): add object linking tools
    Add UniCROSS-style object output with PUBLIC/EXTERN/ENTRY, microlink final image generation with symbol table printing, and microdis support for binary/object inputs. Update assembler docs and smoke 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
2026-05-22 feat(asm): add configurable assembly listing
2026-05-22 fix(tooling): align microasm consumers with mem output
2026-05-22 fix(smallc): add pointer depth const and object-mode tests
2026-05-22 fix(smallc): advance selfhost object compilation
2026-05-22 fix(smallc): split selfhost compiler objects
2026-05-22 refactor(smallc): make split toolchain canonical
2026-05-22 feat(smallc): run pcode backend under microemu
2026-05-22 test(smallc): validate pcode native object calls
2026-05-22 test(smallc): expand pcode backend coverage
2026-05-22 measure(smallc): add selfhost pcode size smoke
2026-05-22 feat(smallc): add pcode indirect function calls
2026-05-22 test(smallc): add pcode selfhost link smoke
2026-05-22 optimize(smallc): compact pcode bytecode
2026-05-22 feat(smallc): add pcode selfhost execution smoke
2026-05-22 feat(smallc): link multiple pcode objects directly
2026-05-23 fix(smallc): diagnose pcode selfhost heap exhaustion
2026-05-31 optimize(smallc): add pcode peephole diagnostics
2026-05-31 optimize(smallc): rewrite live pcode temp roundtrips
2026-06-03 optimize(smallc): compact pcode branches
2026-06-03 optimize(smallc): compact pcode native calls
2026-06-03 optimize(smallc): compact three-argument pcode calls
2026-06-03 optimize(smallc): compact pcode add immediates
2026-06-03 optimize(smallc): compact pcode sub and eq immediates
2026-06-03 optimize(smallc): compact large pcode add immediates
2026-06-03 optimize(smallc): compact pcode zero local stores
2026-06-03 optimize(smallc): compact pcode constant local stores
2026-06-03 optimize(smallc): compact pcode local add pattern
2026-06-03 optimize(smallc): compact pcode tee local stores
2026-06-03 optimize(smallc): compact pcode local returns
2026-06-04 optimize(smallc): move safe pcode compaction into smallcc
2026-06-04 chore: move smallc to standalone repository
